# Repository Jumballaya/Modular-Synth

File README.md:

# Modular Synth, Eurorack compatible

## Contents

1. Case
2. Power Supply
3. Modules
    - VCO

## Case

The case design is currently being worked on.

## Power Supply

The power supply is compatible with the Eurorack 16 pin standard delivering +12V, -12V, +5V and CV/Gate information. The power supply uses a 12V AC wall wart and has power outputs.

## Modules

### VCO

The VCO is still being designed. I am currently planning for 1V/octave with a wave -10V to 10V, either Triangle, Saw or a Square wave with a pulse-width modulation potentiometer as well as a course and fine volume controls.

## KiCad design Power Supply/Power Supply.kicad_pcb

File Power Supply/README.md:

# Power Supply

This power supply uses an L7812, L7912 and LM7805 as voltage regulators to create +12V, -12V and +5V power rails. Each voltage regulator has a 1uF capacitor tied to ground on both the input and output as well as 3 4700uF capacitors as buffer from the power input.

There are 6 IDC, 16 pin, headers for powering modules. The board has each row marked and a number '1' near the red stripe row.

## 3D Render

## Schematic

## Layout

#### Front

#### Back

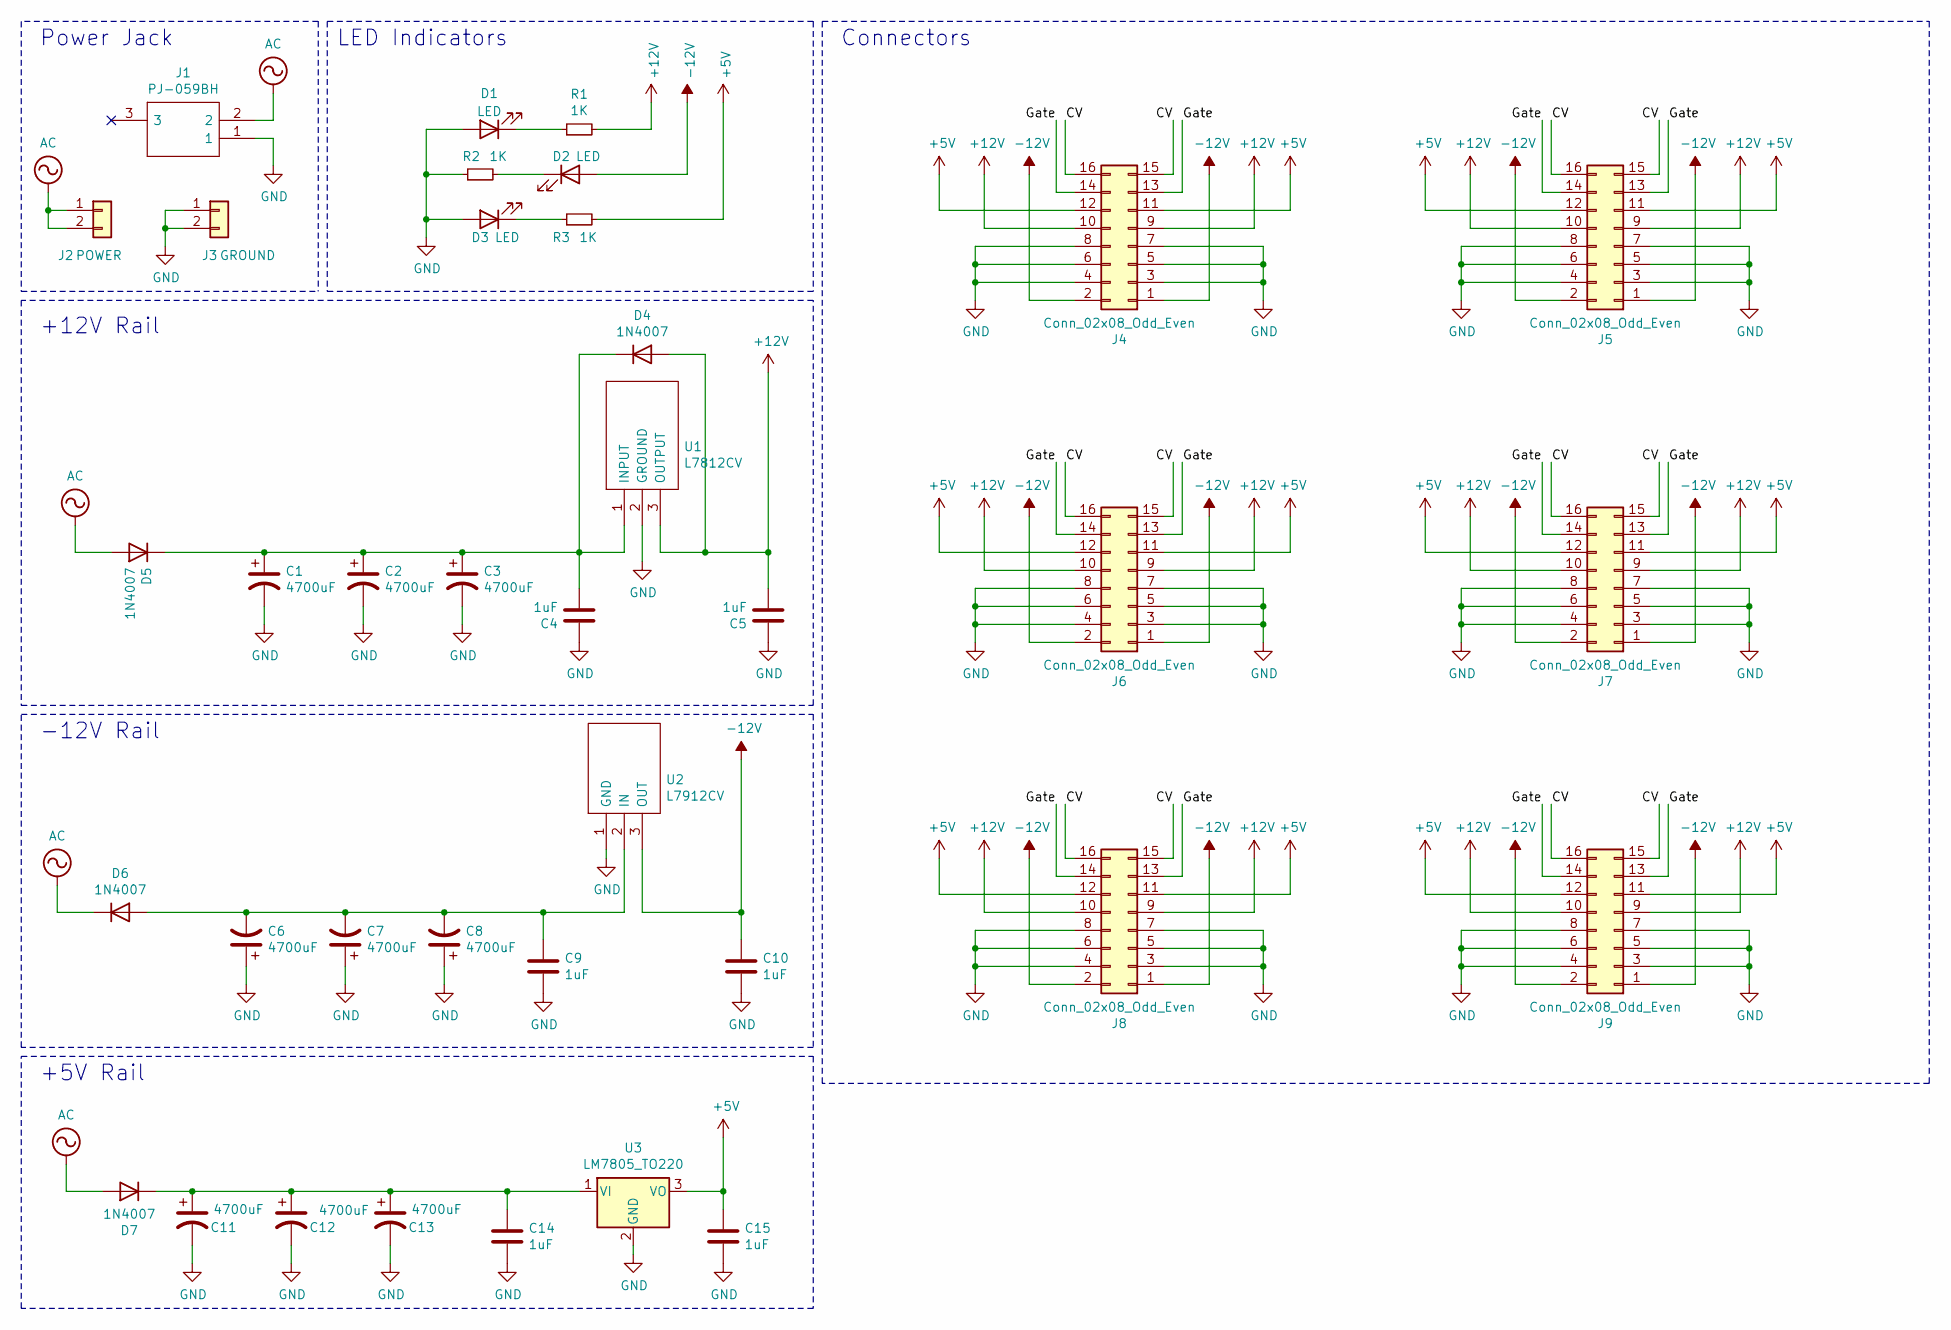
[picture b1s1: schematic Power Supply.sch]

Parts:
C1, C2, C3, C6, C7, C8, C11, C12, C13: 4700uF; CP_Radial_D18.0mm_P7.50mm
C4, C5, C9, C10, C14, C15: 1uF; C_Disc_D5.0mm_W2.5mm_P2.50mm
D1, D2, D3: LED; LED_D5.0mm
D4, D5, D6, D7: 1N4007; D_DO-41_SOD81_P10.16mm_Horizontal
J1: PJ-059BH; PJ059BH; Mouser Part Number 490-PJ-059BH
J2: POWER; PinHeader_1x02_P2.54mm_Vertical
J3: GROUND; PinHeader_1x02_P2.54mm_Vertical
J4, J5, J6, J7, J8, J9: Conn_02x08_Odd_Even; PinHeader_2x08_P2.54mm_Vertical
R1, R2, R3: 1K; R_Axial_DIN0207_L6.3mm_D2.5mm_P10.16mm_Horizontal
U1: L7812CV; TO255P460X1020X2008-3P; Mouser Part Number 511-L7812CV
U2: L7912CV; TO255P460X1020X2008-3P; Mouser Part Number 511-L7912CV
U3: LM7805_TO220; TO-220-3_Vertical

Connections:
+5V: C15.1, J4.11, J4.12, J5.11, J5.12, J6.11, J6.12, J7.11, J7.12, J8.11, J8.12, J9.11, J9.12, R3.2, U3.3 (VO)
+12V: C5.2, D4.2 (A), J4.9, J4.10, J5.9, J5.10, J6.9, J6.10, J7.9, J7.10, J8.9, J8.10, J9.9, J9.10, R1.2, U1.3 (OUTPUT)
-12V: C10.1, D2.2 (A), J4.1, J4.2, J5.1, J5.2, J6.1, J6.2, J7.1, J7.2, J8.1, J8.2, J9.1, J9.2, U2.3 (OUT)
/CV: J4.15, J4.16, J5.15, J5.16, J6.15, J6.16, J7.15, J7.16, J8.15, J8.16, J9.15, J9.16
/Gate: J4.13, J4.14, J5.13, J5.14, J6.13, J6.14, J7.13, J7.14, J8.13, J8.14, J9.13, J9.14
AC: D5.2 (A), D6.1 (K), D7.2 (A), J1.2, J2.1, J2.2
GND: C1.2, C2.2, C3.2, C4.1, C5.1, C6.1, C7.1, C8.1, C9.2, C10.2, C11.2, C12.2, C13.2, C14.2, C15.2, D1.2 (A), D3.2 (A), J1.1, J3.1, J3.2, J4.3, J4.4, J4.5, J4.6, J4.7, J4.8, J5.3, J5.4, J5.5, J5.6, J5.7, J5.8, J6.3, J6.4, J6.5, J6.6, J6.7, J6.8, J7.3, J7.4, J7.5, J7.6, J7.7, J7.8, J8.3, J8.4, J8.5, J8.6, J8.7, J8.8, J9.3, J9.4, J9.5, J9.6, J9.7, J9.8, R2.1, U1.2 (GROUND), U2.1 (GND), U3.2 (GND)
unnamed: C1.1, C2.1, C3.1, C4.2, D4.1 (K), D5.1 (K), U1.1 (INPUT)
unnamed: C6.2, C7.2, C8.2, C9.1, D6.2 (A), U2.2 (IN)
unnamed: C11.1, C12.1, C13.1, C14.1, D7.1 (K), U3.1 (VI)
unnamed: D1.1 (K), R1.1
unnamed: D2.1 (K), R2.2
unnamed: D3.1 (K), R3.1

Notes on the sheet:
-12V Rail
+12V Rail
Power Jack
LED Indicators
+5V Rail
Connectors

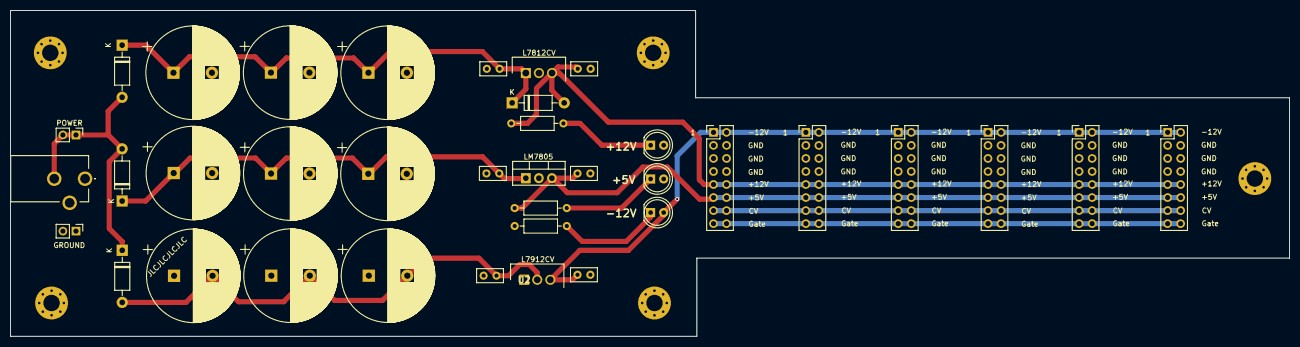
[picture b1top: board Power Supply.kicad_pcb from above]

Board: 2 copper layers, 249.2 x 63.5 mm, 37 parts (0 on the bottom side), 13 nets.

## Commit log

2021-02-10 init + add power supply files
2021-02-10 add images + readme to power supply
